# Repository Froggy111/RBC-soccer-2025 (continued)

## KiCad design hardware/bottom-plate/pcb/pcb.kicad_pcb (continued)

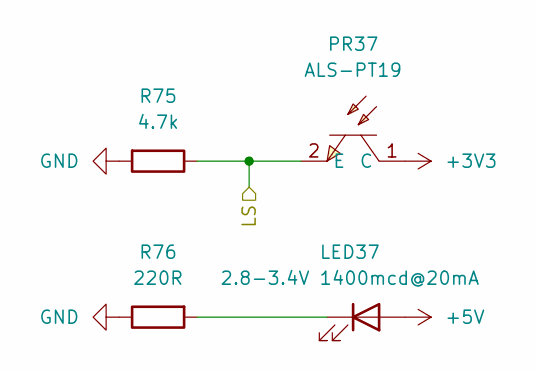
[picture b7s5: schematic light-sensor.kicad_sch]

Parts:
LED37: 2.8-3.4V 1400mcd@20mA; D_0805_2012Metric_Pad1.15x1.40mm_HandSolder
PR37: ALS-PT19; SENSORS-SMD_ALS-PT19; LCSC Part C146233
R75: 4.7k; R_0805_2012Metric_Pad1.15x1.40mm_HandSolder
R76: 220R; R_0805_2012Metric_Pad1.15x1.40mm_HandSolder

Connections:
+3V3: PR37.1 (C); also elsewhere on the board
+5V: LED37.2 (A); also elsewhere on the board
/line sensor array 3/LS5: PR37.2 (E), R75.1; also elsewhere on the board
GND: R75.2, R76.1; also elsewhere on the board
unnamed: LED37.1 (K), R76.2

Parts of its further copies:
LED1, LED2, LED3, LED4, LED5, LED6, LED7, LED8, LED9, LED10, LED11, LED12, LED13, LED14, LED15, LED16, LED17, LED18, LED19, LED20, LED21, LED22, LED23, LED24, LED25, LED26, LED27, LED28, LED29, LED30, LED31, LED32, LED33, LED34, LED35, LED36, LED38, LED39, LED40, LED41, LED42, LED43, LED44, LED45, LED46, LED47, LED48: 2.8-3.4V 1400mcd@20mA; D_0805_2012Metric_Pad1.15x1.40mm_HandSolder
PR1, PR2, PR3, PR4, PR5, PR6, PR7, PR8, PR9, PR10, PR11, PR12, PR13, PR14, PR15, PR16, PR17, PR18, PR19, PR20, PR21, PR22, PR23, PR24, PR25, PR26, PR27, PR28, PR29, PR30, PR31, PR32, PR33, PR34, PR35, PR36, PR38, PR39, PR40, PR41, PR42, PR43, PR44, PR45, PR46, PR47, PR48: ALS-PT19; SENSORS-SMD_ALS-PT19; LCSC Part C146233
R3, R5, R7, R9, R11, R13, R15, R17, R19, R21, R23, R25, R27, R29, R31, R33, R35, R37, R39, R41, R43, R45, R47, R49, R51, R53, R55, R57, R59, R61, R63, R65, R67, R69, R71, R73, R77, R79, R81, R83, R85, R87, R89, R91, R93, R95, R97: 4.7k; R_0805_2012Metric_Pad1.15x1.40mm_HandSolder
R4, R6, R8, R10, R12, R14, R16, R18, R20, R22, R24, R26, R28, R30, R32, R34, R36, R38, R40, R42, R44, R46, R48, R50, R52, R54, R56, R58, R60, R62, R64, R66, R68, R70, R72, R74, R78, R80, R82, R84, R86, R88, R90, R92, R94, R96, R98: 220R; R_0805_2012Metric_Pad1.15x1.40mm_HandSolder

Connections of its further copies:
+3V3: PR1.1 (C), PR2.1 (C), PR3.1 (C), PR4.1 (C), PR5.1 (C), PR6.1 (C), PR7.1 (C), PR8.1 (C), PR9.1 (C), PR10.1 (C), PR11.1 (C), PR12.1 (C), PR13.1 (C), PR14.1 (C), PR15.1 (C), PR16.1 (C), PR17.1 (C), PR18.1 (C), PR19.1 (C), PR20.1 (C), PR21.1 (C), PR22.1 (C), PR23.1 (C), PR24.1 (C), PR25.1 (C), PR26.1 (C), PR27.1 (C), PR28.1 (C), PR29.1 (C), PR30.1 (C), PR31.1 (C), PR32.1 (C), PR33.1 (C), PR34.1 (C), PR35.1 (C), PR36.1 (C), PR38.1 (C), PR39.1 (C), PR40.1 (C), PR41.1 (C), PR42.1 (C), PR43.1 (C), PR44.1 (C), PR45.1 (C), PR46.1 (C), PR47.1 (C), PR48.1 (C); also elsewhere on the board
+5V: LED1.2 (A), LED2.2 (A), LED3.2 (A), LED4.2 (A), LED5.2 (A), LED6.2 (A), LED7.2 (A), LED8.2 (A), LED9.2 (A), LED10.2 (A), LED11.2 (A), LED12.2 (A), LED13.2 (A), LED14.2 (A), LED15.2 (A), LED16.2 (A), LED17.2 (A), LED18.2 (A), LED19.2 (A), LED20.2 (A), LED21.2 (A), LED22.2 (A), LED23.2 (A), LED24.2 (A), LED25.2 (A), LED26.2 (A), LED27.2 (A), LED28.2 (A), LED29.2 (A), LED30.2 (A), LED31.2 (A), LED32.2 (A), LED33.2 (A), LED34.2 (A), LED35.2 (A), LED36.2 (A), LED38.2 (A), LED39.2 (A), LED40.2 (A), LED41.2 (A), LED42.2 (A), LED43.2 (A), LED44.2 (A), LED45.2 (A), LED46.2 (A), LED47.2 (A), LED48.2 (A); also elsewhere on the board
/line sensor array 1/LS1: PR1.2 (E), R3.1; also elsewhere on the board
/line sensor array 1/LS2: PR2.2 (E), R5.1; also elsewhere on the board
/line sensor array 1/LS3: PR3.2 (E), R7.1; also elsewhere on the board
/line sensor array 1/LS4: PR4.2 (E), R9.1; also elsewhere on the board
/line sensor array 1/LS5: PR5.2 (E), R11.1; also elsewhere on the board
/line sensor array 1/LS6: PR6.2 (E), R13.1; also elsewhere on the board
/line sensor array 1/LS7: PR7.2 (E), R15.1; also elsewhere on the board
/line sensor array 1/LS8: PR8.2 (E), R17.1; also elsewhere on the board
/line sensor array 1/LS9: PR9.2 (E), R19.1; also elsewhere on the board
/line sensor array 1/LS10: PR10.2 (E), R21.1; also elsewhere on the board
/line sensor array 1/LS11: PR11.2 (E), R23.1; also elsewhere on the board
/line sensor array 1/LS12: PR12.2 (E), R25.1; also elsewhere on the board
/line sensor array 1/LS13: PR13.2 (E), R27.1; also elsewhere on the board
/line sensor array 1/LS14: PR14.2 (E), R29.1; also elsewhere on the board
/line sensor array 1/LS15: PR15.2 (E), R31.1; also elsewhere on the board
/line sensor array 1/LS16: PR16.2 (E), R33.1; also elsewhere on the board
/line sensor array 2/LS1: PR17.2 (E), R35.1; also elsewhere on the board
/line sensor array 2/LS2: PR18.2 (E), R37.1; also elsewhere on the board
/line sensor array 2/LS3: PR19.2 (E), R39.1; also elsewhere on the board
/line sensor array 2/LS4: PR20.2 (E), R41.1; also elsewhere on the board
/line sensor array 2/LS5: PR21.2 (E), R43.1; also elsewhere on the board
/line sensor array 2/LS6: PR22.2 (E), R45.1; also elsewhere on the board
/line sensor array 2/LS7: PR23.2 (E), R47.1; also elsewhere on the board
/line sensor array 2/LS8: PR24.2 (E), R49.1; also elsewhere on the board
/line sensor array 2/LS9: PR25.2 (E), R51.1; also elsewhere on the board
/line sensor array 2/LS10: PR26.2 (E), R53.1; also elsewhere on the board
/line sensor array 2/LS11: PR27.2 (E), R55.1; also elsewhere on the board
/line sensor array 2/LS12: PR28.2 (E), R57.1; also elsewhere on the board
/line sensor array 2/LS13: PR29.2 (E), R59.1; also elsewhere on the board
/line sensor array 2/LS14: PR30.2 (E), R61.1; also elsewhere on the board
/line sensor array 2/LS15: PR31.2 (E), R63.1; also elsewhere on the board
/line sensor array 2/LS16: PR32.2 (E), R65.1; also elsewhere on the board
/line sensor array 3/LS1: PR33.2 (E), R67.1; also elsewhere on the board
/line sensor array 3/LS2: PR34.2 (E), R69.1; also elsewhere on the board
/line sensor array 3/LS3: PR35.2 (E), R71.1; also elsewhere on the board
/line sensor array 3/LS4: PR36.2 (E), R73.1; also elsewhere on the board
/line sensor array 3/LS6: PR38.2 (E), R77.1; also elsewhere on the board
/line sensor array 3/LS7: PR39.2 (E), R79.1; also elsewhere on the board
/line sensor array 3/LS8: PR40.2 (E), R81.1; also elsewhere on the board
/line sensor array 3/LS9: PR41.2 (E), R83.1; also elsewhere on the board
/line sensor array 3/LS10: PR42.2 (E), R85.1; also elsewhere on the board
/line sensor array 3/LS11: PR43.2 (E), R87.1; also elsewhere on the board
/line sensor array 3/LS12: PR44.2 (E), R89.1; also elsewhere on the board
/line sensor array 3/LS13: PR45.2 (E), R91.1; also elsewhere on the board
/line sensor array 3/LS14: PR46.2 (E), R93.1; also elsewhere on the board
/line sensor array 3/LS15: PR47.2 (E), R95.1; also elsewhere on the board
/line sensor array 3/LS16: PR48.2 (E), R97.1; also elsewhere on the board
GND: R3.2, R4.1, R5.2, R6.1, R7.2, R8.1, R9.2, R10.1, R11.2, R12.1, R13.2, R14.1, R15.2, R16.1, R17.2, R18.1, R19.2, R20.1, R21.2, R22.1, R23.2, R24.1, R25.2, R26.1, R27.2, R28.1, R29.2, R30.1, R31.2, R32.1, R33.2, R34.1, R35.2, R36.1, R37.2, R38.1, R39.2, R40.1, R41.2, R42.1, R43.2, R44.1, R45.2, R46.1, R47.2, R48.1, R49.2, R50.1, R51.2, R52.1, R53.2, R54.1, R55.2, R56.1, R57.2, R58.1, R59.2, R60.1, R61.2, R62.1, R63.2, R64.1, R65.2, R66.1, R67.2, R68.1, R69.2, R70.1, R71.2, R72.1, R73.2, R74.1, R77.2, R78.1, R79.2, R80.1, R81.2, R82.1, R83.2, R84.1, R85.2, R86.1, R87.2, R88.1, R89.2, R90.1, R91.2, R92.1, R93.2, R94.1, R95.2, R96.1, R97.2, R98.1; also elsewhere on the board
unnamed: LED1.1 (K), R4.2
unnamed: LED2.1 (K), R6.2
unnamed: LED3.1 (K), R8.2
unnamed: LED4.1 (K), R10.2
unnamed: LED5.1 (K), R12.2
unnamed: LED6.1 (K), R14.2
unnamed: LED7.1 (K), R16.2
unnamed: LED8.1 (K), R18.2
unnamed: LED9.1 (K), R20.2
unnamed: LED10.1 (K), R22.2
unnamed: LED11.1 (K), R24.2
unnamed: LED12.1 (K), R26.2
unnamed: LED13.1 (K), R28.2
unnamed: LED14.1 (K), R30.2
unnamed: LED15.1 (K), R32.2
unnamed: LED16.1 (K), R34.2
unnamed: LED17.1 (K), R36.2
unnamed: LED18.1 (K), R38.2
unnamed: LED19.1 (K), R40.2
unnamed: LED20.1 (K), R42.2
unnamed: LED21.1 (K), R44.2
unnamed: LED22.1 (K), R46.2
unnamed: LED23.1 (K), R48.2
unnamed: LED24.1 (K), R50.2
unnamed: LED25.1 (K), R52.2
unnamed: LED26.1 (K), R54.2
unnamed: LED27.1 (K), R56.2
unnamed: LED28.1 (K), R58.2
unnamed: LED29.1 (K), R60.2
unnamed: LED30.1 (K), R62.2
unnamed: LED31.1 (K), R64.2
unnamed: LED32.1 (K), R66.2
unnamed: LED33.1 (K), R68.2
unnamed: LED34.1 (K), R70.2
unnamed: LED35.1 (K), R72.2
unnamed: LED36.1 (K), R74.2
unnamed: LED38.1 (K), R78.2
unnamed: LED39.1 (K), R80.2
unnamed: LED40.1 (K), R82.2
unnamed: LED41.1 (K), R84.2
unnamed: LED42.1 (K), R86.2
unnamed: LED43.1 (K), R88.2
unnamed: LED44.1 (K), R90.2
unnamed: LED45.1 (K), R92.2
unnamed: LED46.1 (K), R94.2
unnamed: LED47.1 (K), R96.2
unnamed: LED48.1 (K), R98.2

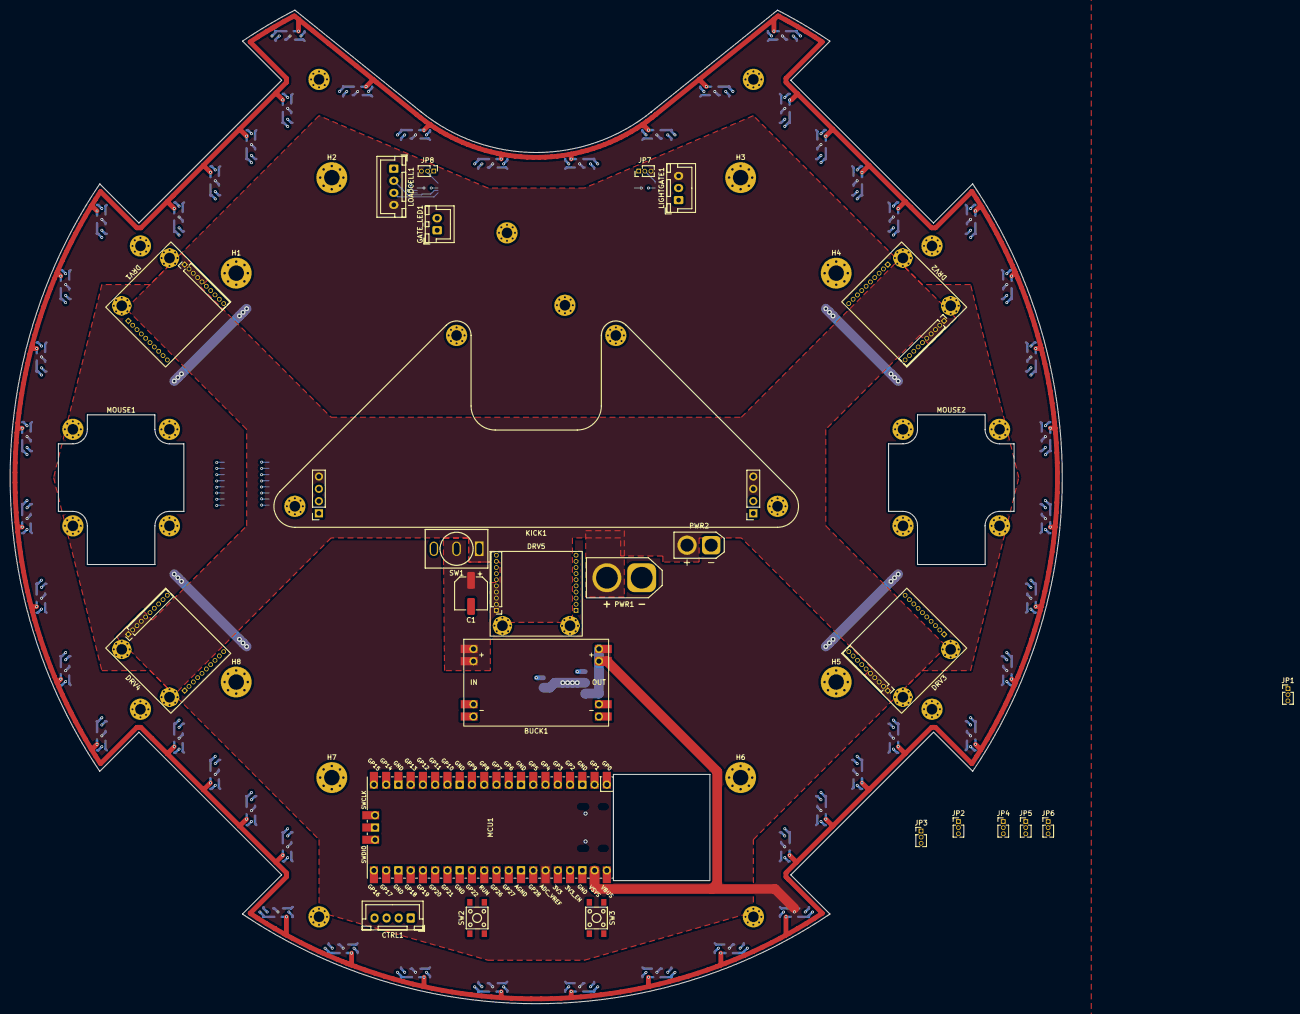
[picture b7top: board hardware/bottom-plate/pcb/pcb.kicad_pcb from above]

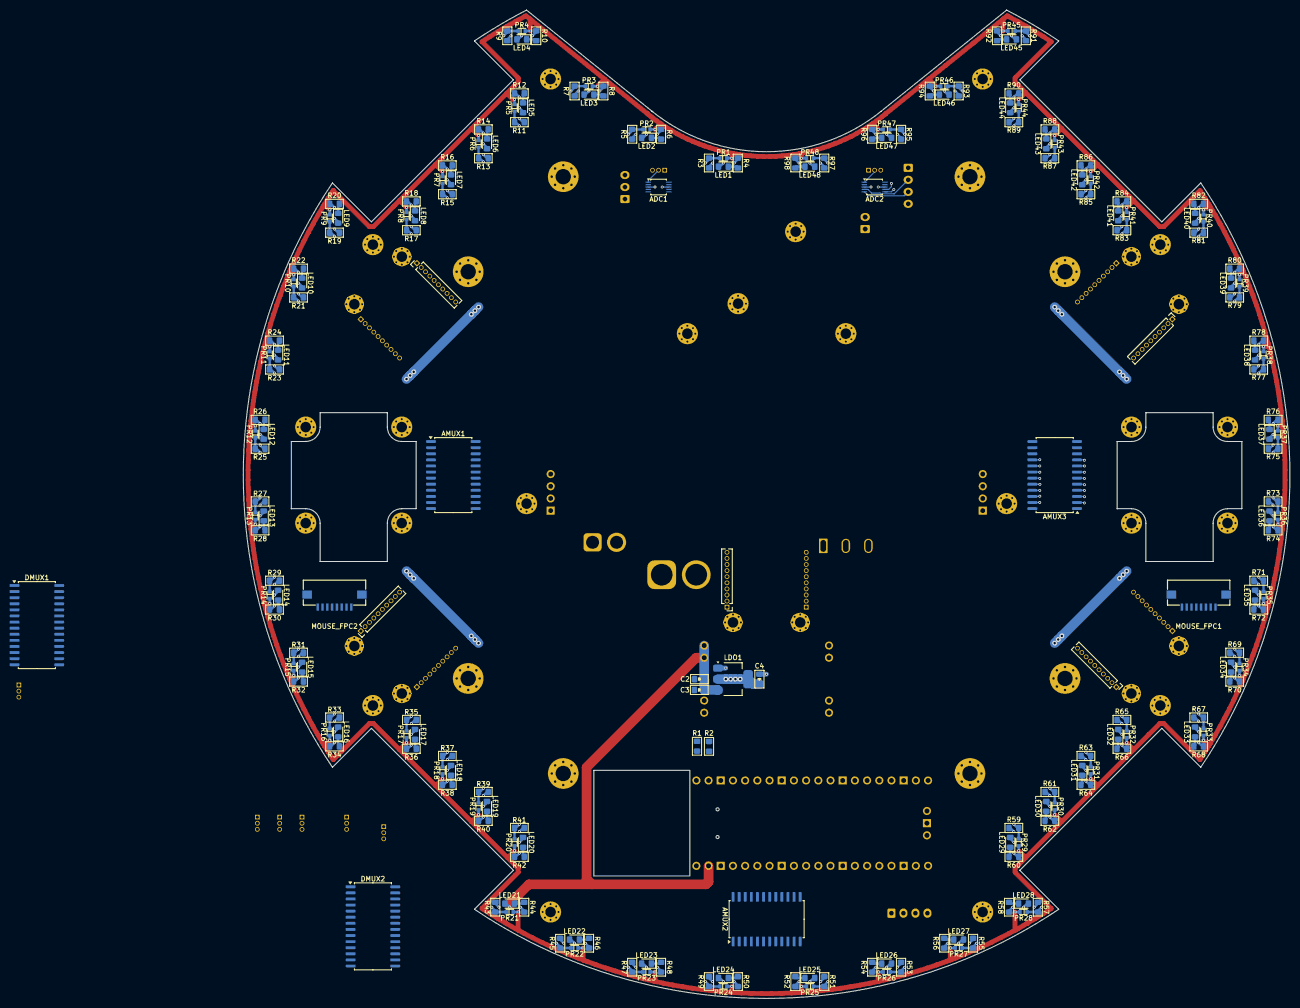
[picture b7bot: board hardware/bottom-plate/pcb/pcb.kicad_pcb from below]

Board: 4 copper layers, 218.0 x 205.9 mm, 253 parts (207 on the bottom side), 177 nets.

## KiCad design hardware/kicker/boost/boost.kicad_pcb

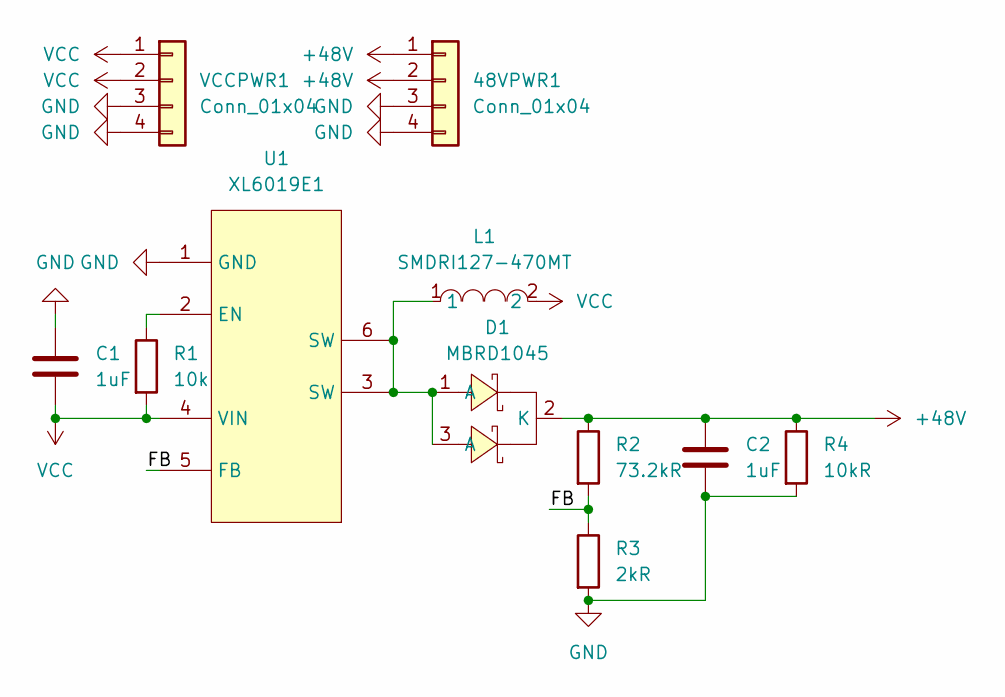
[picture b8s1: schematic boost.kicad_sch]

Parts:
48VPWR1: Conn_01x04; PinSocket_1x04_P2.54mm_Vertical
C1, C2: 1uF; C_1206_3216Metric_Pad1.33x1.80mm_HandSolder
D1: MBRD1045; TO-252-3_L6.5-W5.9-P4.60-LS10.0-BL; LCSC Part C5137764
L1: SMDRI127-470MT; IND-SMD_L12.3-W12.3; LCSC Part C9906
R1: 10k; R_1206_3216Metric_Pad1.30x1.75mm_HandSolder
R2: 73.2kR; R_1206_3216Metric_Pad1.30x1.75mm_HandSolder
R3: 2kR; R_1206_3216Metric_Pad1.30x1.75mm_HandSolder
R4: 10kR; R_1206_3216Metric_Pad1.30x1.75mm_HandSolder
U1: XL6019E1; TO-263-5_L10.2-W9.9-P1.70-LS14.4-TL; LCSC Part C73018
VCCPWR1: Conn_01x04; PinSocket_1x04_P2.54mm_Vertical

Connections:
+48V: 48VPWR1.1, 48VPWR1.2, C2.1, D1.2 (K), R2.1, R4.1
/FB: R2.2, R3.1, U1.5 (FB)
GND: 48VPWR1.3, 48VPWR1.4, C1.1, C2.2, R3.2, R4.2, U1.1 (GND), VCCPWR1.3, VCCPWR1.4
unnamed: D1.1 (A), D1.3 (A), L1.1, U1.3 (SW), U1.6 (SW)
unnamed: R1.1, U1.2 (EN)
VCC: C1.2, L1.2, R1.2, U1.4 (VIN), VCCPWR1.1, VCCPWR1.2

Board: 2 copper layers, 13 parts (7 on the bottom side), 6 nets, no tracks yet.

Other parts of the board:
H1, H2: MountingHole_Pad; MountingHole_2.2mm_M2_Pad_Via

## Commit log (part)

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2025-03-22 edit many rpi scripts and namespace everything
2025-03-22 Add utils and clean up a bunch of code
2025-03-22 :sparkles: Done with loss function!
2025-03-22 :fire: Remove src
2025-03-23 Cam Locxalization done????
2025-03-23 Write test for processor
2025-03-23 half from 500ms to 200ms
2025-03-23 more optimizations, down to 36ms
2025-03-23 Improve a few things with the cam localization
2025-03-23 add analyzer for generated csv
2025-03-23 tweak a few more things
2025-03-23 :bug: Fix randomnization bugs
2025-03-23 :fire: Edit cam tests
2025-03-23 AHHHHH
2025-03-23 add back rpi-direct for easy on-computer compilation
2025-03-23 Implement grid search and fine tune a few other things
2025-03-23 modify for rpi too
2025-03-24 :sparkles: Add ADC!
2025-03-24 Add read_current
2025-03-24 :recycle: Fine tune a ton of things
2025-03-24 :bug: fix a ton of bugs including heading overflow
2025-03-24 optimize a bunch of stuff and write a benchmark tests
2025-03-24 Fix a small wrong field with issue and start chunking
2025-03-24 chunked
2025-03-24 Revert back to chunked
2025-03-24 trying to visualize loss func
2025-03-25 FINALLY correct loss func???
2025-03-25 Correct loss????
2025-03-25 oops fix a few numbers
2025-03-25 Very close
2025-03-25 Rename a ton of variables
2025-03-25 :sparkles: A LOT OF BUGS FIXED I WANA BONK
2025-03-25 :sparkles: hmmmmm threshold script and threshold tuning
2025-03-25 change video resolution
2025-03-25 pid sort of but not building cos max
2025-03-25 fix camera record
2025-03-25 :sparkles: IT FRICKING WORKS OMFG
2025-03-25 fix analyzer script
2025-03-25 more motion changes
2025-03-25 MOTORS it prints the right values
2025-03-25 works quite well wow
2025-03-25 update rpi
2025-03-26 AHHHHH implement camera source
2025-03-26 fix in pins not working
2025-03-26 pullup gpio
2025-03-26 heh 2 works?
2025-03-26 crash prevention
2025-03-26 WOOO IT WORKS MOTORS
2025-03-26 make line sensor and mouse sensor test work
2025-03-26 AONOIDSUIUDISUO
2025-03-26 REVERT >:(
2025-03-26 AHHHHHHH
2025-03-26 IT FRICKIJG WORKS BOTTOM PLATE!!!!! :D ADC
2025-03-26 actually working motor formula sriram
2025-03-26 test!
2025-03-26 All motion stuff
2025-03-26 :sparkles: First parts of comms libs for rpi
2025-03-27 Change again, cuz gpt messed up
2025-03-27 Well... comms compiles
2025-03-27 :sparkles: Add ITRIP and OCP, refractor motor driver
2025-03-27 added setting of pid and vid
2025-03-27 Sync VID PID to top and middle
2025-03-27 Add debug for bottom lib
2025-03-27 fix camera loss generation issues
2025-03-27 Refractor cam loc
2025-03-27 refractored headers (impl not touched yet)
2025-03-27 mcp23s17 refractored, adding interrupts now
2025-03-27 Update to not use libusb
2025-03-27 PID Works???
2025-03-27 Ehhhh some changes
2025-03-27 AAAAAAHHHH MOUSE SENSOR
2025-03-27 SENDINF WORKS GPT U FRICKING LEGEND
2025-03-28 :art:
2025-03-28 Edit attach listener so that we get to provide a device to attach a listener to
2025-03-28 Refractored comms lib to use different identifiers
2025-03-28 fixed usb vid pid setting
2025-03-28 :sparkles: Comms lib fully done
2025-03-28 added interrupts to MCP23S17
2025-03-28 standardised naming
2025-03-28 actually fixed
2025-03-28 updated pins iface
2025-03-28 ousdhfoudshf
2025-03-28 made mcp23s17 actually follow from_isr
2025-03-28 acutally fixed MCP23S17
2025-03-28 Refractor the entire driver lib for thre new pins lib
2025-03-28 :sparkles: Refractor camera a bit ish and start on source code
2025-03-28 small cleanup on motion lib
2025-03-28 cam 20%
2025-03-28 made debug take const char instead
2025-03-28 changed mcp23s17 to use log funcs and added detaching and disabling/enabling interrupts
2025-03-28 sorting at pinmap
2025-03-28 interrupts for digital pins done
2025-03-28 pins lib done (not checked compile yet)
2025-03-28 pins lib actually compiles now?
2025-03-29 fix driver lib
2025-03-29 fixed digital pins
2025-03-29 oops
2025-03-29 init in motor
2025-03-29 INOUIIII
2025-03-29 i am dumb.
2025-03-29 Add debugging info
2025-03-29 fixed logic
2025-03-29 Fixed?
2025-03-29 MORE ISSUES AH
2025-03-29 More logs
2025-03-29 fixed picotool reset
2025-03-29 BRAIN GONE
2025-03-29 ok this one compiles
2025-03-29 asdasdas
2025-03-29 try this?
2025-03-29 SUDHFOSUDH
2025-03-29 soudhfousdh
2025-03-29 eh v2
2025-03-29 dont commit log files
2025-03-29 klil
2025-03-29 why no worksiudhfousdhf
2025-03-29 switch bcasse stupidness
2025-03-29 sdhjfoiusdh
2025-03-29 Use new comms lib
2025-03-29 SKip nfalt if reg is 0
2025-03-29 clear fault and move on if got nfault high
2025-03-29 kick test done
2025-03-29 Add regression
2025-03-29 Finish bottom plate firmware kinda
2025-03-29 Smallf ix
2025-03-29 Potentially fix camera loc tilted thing
2025-03-29 Fix RPI
2025-03-29 hmmmmmm :think:
2025-03-29 goalpost
2025-03-29 make loss func work for tilted
2025-03-29 Partially Working Particle Filter
    Converges at right position but wrong heading, probably a matter of changing some weights
2025-03-29 hmmm
2025-03-29 Add fuzziness???
2025-03-29 AHHHHHH TRY MAKE CAM LOC WORK WITH FUZZI
2025-03-30 PF WORKS (95+% accurate ish)
2025-03-30 Update rpi and correct a few things
2025-03-30 YAY??????
2025-03-30 Fixed PF frfrfr
2025-03-30 This shld work?
2025-03-30 dasoijasiodhjaios
2025-03-30 new motor driver update
2025-03-30 SDIJOSJDIOSNDO
2025-03-30 wo bu yao zuo anymore
2025-03-30 dasdsadsa
2025-03-30 this is a bad commit but im just syncing this
2025-03-30 started on IR (?)
2025-03-31 Revert :cry:
2025-03-31 Done adapting bottom plate
2025-03-31 Better detection of goalpost
2025-03-31 hmmmmmm
2025-03-31 soudfhs
2025-03-31 Add wiringPi
2025-03-31 Wiring pi compiles
2025-03-31 Add ADC
2025-03-31 AHHHH emergency stop works?
2025-03-31 Update software
2025-03-31 Remove sync sysroot
2025-03-31 try to fix for wiringpi
2025-03-31 wiringpi compiles for pi
2025-03-31 yooo its better goal detection
2025-03-31 updated comms with init fn, ping func and identifier query task
    havent checked if it compiles yet on middle and top
2025-03-31 :sparkles: UPDATE
2025-03-31 Find midpoints of quadrilaterals and shifted the file to the right place
    moved from middle to rpi-direct under libs >> camera >> scripts
2025-03-31 fixed debug const char in middle and top
2025-03-31 AHHHH
2025-03-31 IR lib
2025-03-31 IR test
2025-03-31 made comms globally link
    comms not linked in many places but implicitly linked through debug this
    prevents possible weird issues
2025-04-01 added IR header
2025-04-01 Comms lib works?
2025-04-01 yooo
2025-04-01 Update pi
2025-04-01 IR test builds
2025-04-01 ooh make bot run?
2025-04-01 Add debugging
2025-04-01 Estimate heading using goal post midpoint
2025-04-01 add IR to software/rpi, and remove IDLE mode
2025-04-01 fix small bottom plate cannot build issue
2025-04-01 move IR
2025-04-01 Add kicker
2025-04-01 Add a bunch of rpi firmware
2025-04-01 fix a lot of rpi and bottom bugs
2025-04-01 added blink to builtin task of comms
2025-04-01 copied changes to middle and top comms
2025-04-01 made things static
2025-04-01 fix a bunch of stuff on rpi
2025-04-01 updated gitignore
2025-04-01 LOTS of bug fixes
2025-04-01 Added IR ball detection
    Given the values for each sensor (numbers follow numbering in KiCad), finds the direction the bot must travel to reach the bot as well as the distacne. However, this distance is currently arbitrary c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
2025-04-01 Update a lot of stuff
2025-04-01 moved led to before wait for cdc connect
2025-04-01 whattt
2025-04-01 made main task not delete itself
2025-04-01 asdasd
2025-04-01 Updated PF to get velocity from IMU rather than mouse sensor
2025-04-01 maybe fixed crash
2025-04-01 i waht the bomnk
2025-04-01 :sparkles: Update comms lib and everythinb around it
2025-04-02 aaa fixed top imu
2025-04-02 AHHHHHHHHHHH
2025-04-02 idk what shit i did but ajr wants me to commit
2025-04-02 Ball detection test (without LEDs)
2025-04-02 :sparkles: Rip comms::USB_CDC.printf :(
2025-04-02 Got bottom pico logs :D
2025-04-02 cleaned up pi write
2025-04-02 iT SPINS??? WRONG RPM
2025-04-02 commit ~ljy
2025-04-02 heh 2 issues now: motor driver intiialization randomly failing, and also wrong duty cycle sending?
2025-04-02 jiayi what did u do
2025-04-02 OK, 1000 received
2025-04-02 Modify a bunch of printfs
2025-04-02 BOT WORKS
2025-04-02 Refractored some pi
2025-04-02 Fix estop
2025-04-02 YAY correct direction
2025-04-02 estop works too
2025-04-02 adioshdioash
2025-04-02 whatever ive done for IMU so far
2025-04-02 setup strategy
2025-04-02 :sparkles: Update RPI direct
2025-04-02 Change to full particle search with optimizations
2025-04-02 Add debug colours
2025-04-02 PID changes
2025-04-02 Fixed Position PID
2025-04-02 :sparkles: Add chunking
2025-04-03 This kinda works?
2025-04-03 More PID Fixes, not this is not complete
2025-04-03 add it to rpi
2025-04-03 update middle plate
2025-04-03 IMU lib + fusion for correction
2025-04-03 imu calibration setup
2025-04-03 imu test
2025-04-03 i wan die
2025-04-03 AAAAH ANOTHER PID FIX
2025-04-03 This should probably be it for PID hopefully
2025-04-03 asdasdioasiodashid
2025-04-03 ir fix?
2025-04-03 adalidjioadoasdiaosdaos
2025-04-03 IMU stuff
2025-04-03 Port rpi-direct to rpi
2025-04-03 clauded imu calibration
2025-04-03 Integrate IMU into cam
2025-04-03 removed logging from IR it works now
2025-04-03 maybe motor accel limiting on pico
2025-04-03 slowed down IR sending
2025-04-04 try this
2025-04-04 try this more
2025-04-04 try this again
2025-04-04 clowning
2025-04-04 sysclk bs
2025-04-04 try againjksdfbgoushd
2025-04-04 try againspsohdoufh
2025-04-04 im fucking dumb
2025-04-04 verify
2025-04-04 verify again
2025-04-04 see if vals are correct
2025-04-04 sdofsduh
2025-04-04 reverted wrong fixes
2025-04-04 motion controller global
2025-04-04 reverted doing accels on pico side
2025-04-04 shifted goal detection to rpi-direct
2025-04-04 maybe actually working accels
2025-04-04 works
2025-04-04 Sync rpi with rpi-direct
2025-04-04 motor wrappers
2025-04-04 Hmm sync rpi
2025-04-04 rpi-direct
2025-04-04 oshdoufhsd
2025-04-04 shdfousdhf
2025-04-04 prob not the issue
2025-04-04 fixed typo
2025-04-04 idfk
2025-04-04 OAHSUOFAHS AAAAA
2025-04-04 jsudohfousdhf
2025-04-04 strat stuff
2025-04-04 it works now????
2025-04-04 fuck compiler
2025-04-04 synced rpi and rpi-direct
2025-04-04 Goalpost detection + midpoint of bottom line
2025-04-04 Converted goal detection into c++
2025-04-04 Sync with rpi-direct
2025-04-04 Move new rpi and bottom to new rpi and new bottom, and add back old rpi and old bottom
2025-04-04 Add goalpost detection
2025-04-04 low latency cdc + commented out camloc
2025-04-04 idfk idfk idfk idfk what the hell hardware ????hawrda-9fousd hardwareijk khxbuimnabsdkufhus hardware ihshduiohajbhardware???ouhiunxs harwdwareabiodhfsk hwaredaderuahkdh haradweraer ahaefaskjha hrawde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
2025-04-04 Remove all the new folders
2025-04-04 adasidhsaudasiodah
2025-04-04 Ball detection (detects all IR points)
2025-04-04 Updated goalpost detection cpp
2025-04-04 Converted ball detection into an actual c++ project
2025-04-05 Goalpost detection done
2025-04-05 asdoiawhduiahs
2025-04-05 button clicking to run exe or stop exe script
2025-04-05 :sparkles: Add ball detection
2025-04-05 attack stuff
2025-04-05 partially finishedball detection cpp test
2025-04-05 Added finding area of goalpost
2025-04-05 test works
2025-04-05 AHHHHHHHHHH
2025-04-05 asasdsa
2025-04-05 fuck ajr
2025-04-05 the hell
2025-04-05 fixed
2025-04-05 added firmware self rebooting
2025-04-05 dasdsak
2025-04-05 remove possible crash
2025-04-05 optimised line sensors and decreased poll rate
2025-04-05 uhhh revert the funny
2025-04-05 Run.py done
2025-04-05 line sensor evade vectors
2025-04-05 Limit to 4000 duty cycle
2025-04-05 add normalization to this scaling thing
2025-04-05 ball.hpp .cpp and procesor updated
    the main file is how i impled it
2025-04-05 line sensor evade
2025-04-05 Fix strategy ish
2025-04-05 line sensors dont recieve for some reason
2025-04-05 Fixing some cam stuff
2025-04-05 Try to maek IR ball track work?
2025-04-06 defender stuff
2025-04-06 fixed motors
2025-04-06 no logging for bottom, fixes it
2025-04-06 integrated defender logic with line sensor evasion
    resolve 2 vecs then add
